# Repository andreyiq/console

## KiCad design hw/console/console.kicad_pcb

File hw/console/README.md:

# hw/console — схема платы v2 в KiCad 9

Открывать: `kicad hw/console/console.kicad_pro`.

## Статус: разработка, не финал

**Ничего из решённого не является окончательным.** Плата не изготовлена, срок
не горит, тираж не заказан — значит любую деталь, номинал, габарит, топологию
и сам выбор технологии можно и **нужно** пересматривать, если появился повод.

Отсюда рабочее правило: **когда во что-то упираемся — двигаем то, во что
упёрлись, а не проламываемся.** Не влезает деталь — меняем деталь. Не
складывается разводка — меняем размещение или габарит платы. Мешает принятое
раньше решение — обсуждаем его заново, а не обходим.

Записанное в этих документах — это состояние обсуждения на сегодня вместе с
обоснованием, а не приговор. Обоснование как раз затем и пишется: чтобы через
месяц было видно, на чём решение держится, и можно было честно проверить, не
рассыпалось ли оно. Уже так и вышло: планка «`ISAT` ≥ 2 А, `DCR` < 50 мΩ» была
записана как требование, а оказалась перестраховкой — живая плата Xassette
работает на 176 мΩ (02-power.md §5). Решение переписано.

Ссылки на источники (даташит, MangoPi, Xassette) при этом остаются жёсткими:
меняться может **наше** решение, но не факт, на который оно опирается.

## Источники истины

Ровно три, больше ничего:

| | |
|---|---|
| **Даташит** | `docs/mangopi/f133_datasheet_v1.2.pdf` и `docs/chips/<партномер>_<LCSC>.pdf` |
| **MangoPi** | `docs/mangopi/mq_sch_v1.6.pdf` — серийная плата на том же F133-A |
| **Xassette** | `../ref/Xassette-Asterisk/` — вторая живая плата на F133, и единственная опора, где есть **сама плата**, а не только схема: `hw/XassetteAsterisk.kicad_pcb` отвечает на вопросы про стек, термопад и переходные |

Всё остальное — не источник. В частности [`../BOARD-draft.md`](../BOARD-draft.md)
**недостоверен**: он писался по ходу дела, мешает проверенные числа с
рассуждениями, и в нём уже находилось прямое противоречие самому себе.
Ссылаться на него нельзя, он оставлен как список тем для перепроверки.
[`../TZ.md`](../TZ.md) отвечает только на вопрос «что должно быть на плате»,
[`../CHIPS.md`](../CHIPS.md) — «какие микросхемы», ни один из них не источник
электрических решений.

**Правило: ни одного номинала и ни одной цепи без ссылки на источник.** Если
факта нет ни в даташите, ни на двух платах — это не факт, а допущение, и оно
помечается как допущение вместе с тем, чем рискуем.

## Порядок работы — по блокам

Блок = микросхема (или группа) из [`../CHIPS.md`](../CHIPS.md). На каждый блок
заводится документ в [`blocks/`](blocks/) с жёсткой структурой:

1. **Микросхемы** — какие пункты CHIPS.md закрывает блок
2. **Из даташита** — выдержки с номером таблицы или параграфа
3. **MangoPi** — что реально сделано, с номером страницы и позициями
4. **Xassette** — то же, с refdes из нетлиста
5. **Расхождения** — где референсы спорят друг с другом или с даташитом
6. **Что рисуем** — решение, каждая строка со ссылкой на пункты выше
7. **Допущения и открытые вопросы** — всё, что не подтверждено источником

Итерация: собрать документ блока → обсудить открытые вопросы → дополнить
[`../CHIPS.md`](../CHIPS.md) закупкой → нарисовать блок → показать глазами →
ERC и netlist → следующий блок.

| Блок | Микросхемы (CHIPS.md) | Документ | Статус |
|---|---|---|---|
| 1 Кнопки | — | [01-buttons.md](blocks/01-buttons.md) | **нарисовано**, 10 деталей |
| 2 Питание | §2 `SY8089AAAC`×3, §3 `TP4056`, §7 движок, §8 банка, §10 power path | [02-power.md](blocks/02-power.md) | **нарисовано**, 48 деталей |
| 3 USB и FEL | §9 `USBLC6-2SC6` | [03-usb.md](blocks/03-usb.md) | **нарисовано**, 5 деталей |
| 4 Хранение | §6 `W25Q32` | [04-storage.md](blocks/04-storage.md) | **нарисовано**, 16 деталей |
| 5 Звук | §5 `PAM8301` | [05-audio.md](blocks/05-audio.md) | **нарисовано**, 11 деталей |
| 6 Дисплей | §4 подсветка | [06-display.md](blocks/06-display.md) | **нарисовано**, 13 деталей |
| 7 Такт и сброс | — | [07-clock-reset.md](blocks/07-clock-reset.md) | **нарисовано**, 10 деталей |
| 8 Развязка и КТ | §1 `F133-A` | [08-decoupling.md](blocks/08-decoupling.md) | **нарисовано**, 33 детали |
| 9 UART, JTAG, светодиод | — | [09-debug.md](blocks/09-debug.md) | **нарисовано**, 8 деталей |
| 10 Механика и плата | — | [10-mech.md](blocks/10-mech.md) | контур, механика посажена, разводки нет |

## Как устроен лист

**Один лист A2**, `console.kicad_sch`. F133 целиком в середине, обвязка вокруг
него девятью блоками в пунктирных рамках. Раскладка скопирована со стр. 3 схемы
MangoPi (`docs/mangopi/mq_sch_v1.6.pdf`) — это плата на том же чипе, и она
устроена так же.

Правило раскладки: **блок стоит с той стороны корпуса, откуда выходят его
выводы.** Символ повторяет корпус, поэтому сторона известна заранее:

| Выводы | Сторона | Блок |
|---|---|---|
| 1..6, 118..128 `PG` | лево-верх и верх-лево | 1 Кнопки |
| 7..13 `PF`, 14..19 `PC` | лево | 4 Хранение |
| 20..30 PLL/DCXO/RTC/LDO | лево-низ | 7 Такт и сброс |
| 31..45 `PE` | лево-низ и низ-лево | 9 UART, JTAG, светодиоды |
| 46..51 SYS/DRAM | низ-центр | 8 Развязка и контрольные точки |
| 52..76 `PD` | низ-право и право-низ | 6 Дисплей |
| 87..100 аудио | право-верх | 5 Звук |
| 101..117 ADC/USB/CORE | верх | 2 Питание, 3 USB и FEL |

Раскладка задаёт только геометрию. Что внутри блока — в его документе
в [`blocks/`](blocks/).

## Как соединяется

Проводов между блоками нет — всё на **глобальных метках**, как у MangoPi. Для
128-выводного чипа это единственный читаемый вариант: цепь называется один раз
у вывода F133 и один раз у потребителя, а не тянется через весь лист.
Локальные провода — только внутри блока (делитель, RC, развязка).

## Библиотеки

Обе локальные, лежат в `lib/`, подключены через `${KIPRJMOD}` — проект
открывается на любой машине без установки библиотек.

| | |
|---|---|
| `lib/console.kicad_sym` | символ F133-A. Генерируется, руками не править |
| `lib/parts.kicad_sym` | то, чего нет в штатных библиотеках: `SY8089AAAC` (по даташиту) и рельсы `VSYS`, `+0V9`. Пишется руками |
| `lib/console.pretty` | футпринты платы. `eLQFP-128 ... EPAD_5.72mm` взят из `../lib/allwinner_SiPs_kicad_lib` и обновлён до формата KiCad 9 |

### Символ F133-A

Собирается скриптом из распиновки даташита:

```
python3 hw/console/tools/gen_f133_sym.py
```

Скрипт правит **две** копии символа: `lib/console.kicad_sym` и вшитую в
`console.kicad_sch` секцию `lib_symbols` — KiCad библиотеку при открытии не
перечитывает, и правка распиновки, не доехавшая до листа, разъезжается молча.

129 выводов (128 + `EPAD`), один юнит, корпус 119 × 114 мм. Выводы разложены
**в порядке нумерации eLQFP128** — 1..32 слева сверху вниз, 33..64 снизу слева
направо, 65..96 справа снизу вверх, 97..128 сверху справа налево. Проверено по
футпринту: лапка 33 в левом нижнем углу, 97 в правом верхнем. То есть символ
читается как сам корпус, и при разводке сразу видно, с какой стороны выходит
цепь. Функциональные зоны нарисованы поверх — короткой линией от края и
подписью.

Исходник распиновки — `F133_Datasheet_V1.2.pdf`, таблица 4-2. Библиотека
Xassette (`../ref/Xassette-Asterisk/hw/lib/F133.lib`) использовалась для
сверки, в ней нашлись три расхождения с даташитом, здесь они исправлены:

| Вывод | У Xassette | В даташите |
|---|---|---|
| 47 | `DZQ` | `NC` — но обе платы ставят туда 240 Ω, поэтому тип `passive` и резистор мы тоже ставим (08-decoupling.md §5) |
| 51 | `VDD-SYS0` (дубль) | `VDD-SYS1` |
| 25 | `XX32KIN` | `X32KIN` |

Плюс к этому в символе:

- **выводы 107–111 помечены `no_connect`** — CVBS IN есть только у F133-B.
  У даташита на это отдельная таблица различий версий, Table 7-1 на стр. 74:
  «107 | NC | VCC-TVIN». Обе референсные платы вывод 107 подключают, потому
  что рисовались и под F133-B; разбор — 08-decoupling.md §2.4;
- **`EPAD` = `GND`** — отдельных выводов земли у корпуса нет, вся цифровая
  земля идёт через термопад. Значит термопад обязан быть пришит переходными
  к нижнему слою, это не только теплоотвод;
- **вывод 27 `RESET`** — тип `I, OD`, домен **`VCC-RTC` = 1.8 В**, не 3.3.
  Подтяжка и кнопка сброса должны сидеть на `+1V8`.

## Каркас листа

```
python3 hw/console/tools/scaffold.py
```

Одноразовый скрипт: создаёт лист, рамки блоков, таблицы библиотек и ставит
F133. Уже существующие файлы **не трогает** — схему, которую правили руками,
он не затрёт. UUID детерминированные, поэтому на чистой папке результат
повторяется побайтово.

`console.kicad_pro` скриптом не создаётся — он взят от платы v1 и почищен.

Две грабли, на которые скрипты уже наступили и больше не наступают:

- **координаты символа обязаны быть кратны 1.27 мм.** Середина A2 — это 297.0,
  что не кратно, и все 129 выводов уезжают с сетки (`endpoint_off_grid`).
  Берём 297.18 = 117 × 2.54.
- **`(justify center)` в свойстве символа парсер библиотеки не принимает** —
  библиотека молча перестаёт грузиться целиком. По центру и так по умолчанию,
  просто не указывать.

## Сверка с референсом Xassette

`kicad-cli` схему Xassette не открывает — это legacy-формат KiCad 5. Поэтому
свой разбор:

```
python3 hw/console/tools/xassette_net.py U1 U3 U4 U5   # цепь на каждом выводе
python3 hw/console/tools/xassette_net.py --net +1V8 +3V3   # состав цепи
```

Цепи собираются union-find'ом по концам проводов, junction'ам, меткам и
power-символам.

## Сверка со схемой MangoPi

Она есть только в PDF, но PDF векторный, поэтому её тоже читаем как схему, а
не как картинку:

```
python3 hw/console/tools/mangopi_net.py --page 3 --trace 520 710   # цепь в точке
python3 hw/console/tools/mangopi_net.py --page 3 --at 520 710      # что рядом
python3 hw/console/tools/mangopi_net.py --page 3 --label VCC-DRAM  # цепь по имени
```

`pdftocairo -svg` отдаёт точные концы каждого отрезка; провода там зелёные,
точки соединения — залитые кружки того же цвета. Отрезки объединяются в цепь
по совпадению концов, а касание конца к середине другого отрезка считается
соединением **только** при наличии точки. Имена цепей и номера выводов берутся
из `pdftotext -bbox` и привязываются к проводу по координатам.

Так надо потому, что чтение кропов глазами дважды подряд дало неверный ответ:
резистор `R40 680K` был принят за делитель соседнего преобразователя (номинал
совпадает), а кнопка сброса `S2` не найдена, потому что искалась не на той
странице. Кроп через `pdftoppm` остаётся, но уже как иллюстрация к тому, что
посчитал нетлистер.

Что уже вытащено этими двумя способами — в документах блоков, [`blocks/`](blocks/).

## Плата

```
python3 hw/console/tools/pcb01_outline.py    # контур, крепёж, разметка
# в KiCad: Update PCB from Schematic (F8)    — CLI для этого нет
python3 hw/console/tools/pcb01_outline.py    # F8 сносит крепёж `H*`, вернуть
python3 hw/console/tools/pcb00_sync.py       # корпуса под то, что в схеме
python3 hw/console/tools/pcb02_place.py      # посадка механики, с блокировкой
python3 hw/console/tools/pcb03_blocks.py     # черновая раскладка блоков
python3 hw/console/tools/pcb04_fine.py      # точная посадка, где место задано
python3 hw/console/tools/pcb05_text.py      # ссылки на Fab, шелкографии нет
python3 hw/console/tools/pcb_run.py         # разводка целиком и сводка
```

Последний шаг — весь круг разводки одной командой: веер из-под F133, свой
волновой трассировщик, добор поверх готового, заливки, сшивка и добивка земли,
и в конце сводка с DRC. Добор идёт дольше всего остального вместе, поэтому в
обычной итерации `--no-more` (210 секунд против получаса). Подробно и с
замерами — [10-mech.md §8.3](blocks/10-mech.md).

Все шесть шагов размещения идемпотентны и не трогают чужого: `pcb01` заново кладёт только
свою графику и крепёж, `pcb02` и `pcb04` блокируют то, что посадили, `pcb03`
двигает исключительно незаблокированное. Значит ручную правку размещения они
не затрут.

Правила процесса, координаты и открытые вопросы — [10-mech.md](blocks/10-mech.md).
Собственные правила DRC (одно: площадкам `U1` между собой разрешено 0.15 мм,
потому что таков сам `eLQFP-128`) — в `console.kicad_dru`.

Проверка платы:

```
python3 hw/console/tools/audit_pcb.py
```

Семнадцать проверок того, чего нет в DRC: зона банки, развязка у своих выводов,
минимальное сверло, что под панелью на лице только разъём шлейфа, раскладка
баков по даташиту, состав платы против схемы цепь за цепью. DRC она вызывает
сама и печатает сводкой. Каждая проверка показывает, сколько объектов
посмотрела, — иначе не отличить «чисто» от «сломано».

## Проверка

```
python3 hw/console/tools/audit.py
```

Шестнадцать проверок, каждая печатает, сколько объектов посмотрела. Половину
из них ERC не делает вовсе: Т-образное соединение без точки, метка не на
проводе, наложенные провода, деталь без поля `Источник`, корпус без площадки
под вывод символа, похожие имена цепей. Сейчас все шестнадцать дают ноль.

Отдельно то же самое руками:

```
kicad-cli sch erc           -o /tmp/erc.rpt      hw/console/console.kicad_sch
kicad-cli sch export netlist -o /tmp/console.net  hw/console/console.kicad_sch
kicad-cli sch export pdf     -o /tmp/console.pdf  hw/console/console.kicad_sch
```

**Нарисованы все девять блоков: ERC даёт 0 нарушений.** Число падало по мере
работы: 160 до блока 8, 104 до блока 3, 62 до блока 1, 46 до блока 5, 23 до
блока 9. Ноль означает ровно одно — у каждого из 128 выводов F133 есть либо
цепь, либо крестик «не подключать», и ни одна цепь не осталась висеть в
воздухе. Это не означает, что схема верна: ERC не знает ни номиналов, ни того,
что делает софт.

**Netlist смотреть обязательно, картинки мало.** Провод, нарисованный
правильно, может оказаться разорванным: KiCad считает соединением только конец
провода или точку с junction, поэтому провод обязан быть разрезан там, где к
нему что-то подключается. На печати такая ошибка неотличима от исправной
схемы — в блоке 2 так молча распалась обратная связь канала 0.9 В.

## Как рисуются блоки

Весь чертёж воспроизводится из скриптов:

```
for b in 01_buttons 02_power 03_usb 04_storage 05_audio \
         06_display 07_clock_reset 08_decoupling 09_debug; do
    python3 hw/console/tools/block$b.py
done
```

Прогон в этом порядке даёт **побайтово тот же файл**, что лежит в репозитории:
проверено. Порядок важен только для побайтовости — содержимое от него не
зависит, каждый блок трогает лишь свою рамку и свои зоны у выводов F133.

Каждый блок рисует свой скрипт `tools/blockNN_*.py`, общая машинерия — в
`tools/kicadsch.py`. Модуль печатает те же s-выражения, что писались бы руками;
библиотек KiCad в нём нет. Он же считает координаты выводов при повороте
символа — попасть в вывод надо точно, а руками это и есть главный источник
молчаливых обрывов. Скрипт блока идемпотентный:
перед вставкой выкидывает из схемы всё, что лежит внутри рамки своего блока, и
кладёт заново, — соседние блоки при этом не страдают, а UUID детерминированные,
поэтому повторный запуск не даёт diff'а на пустом месте.

У каждой детали заполнено поле `Источник` — раздел документа блока, откуда взят
номинал. Правило «ни одного номинала без ссылки на источник» проверяется прямо
по схеме, а не на доверии.

Грабли, на которые скрипты уже наступили и больше не наступают:

- `(hide yes)` внутри `(effects)` **не срабатывает, если рядом нет
  `(justify)`** — служебные ссылки `#PWR`/`#FLG` из-за этого печатались в PDF;
- **номер блока обязан входить в ссылку** служебного символа (`#PWR700`, а не
  `#PWR000`): иначе каждый блок начинает нумерацию с нуля и выдаёт ссылки,
  уже занятые соседом;
- `✓` и подобные знаки штриховой шрифт KiCad не рисует — в PDF выходит пустой
  квадрат. В подписях только то, что есть в шрифте.

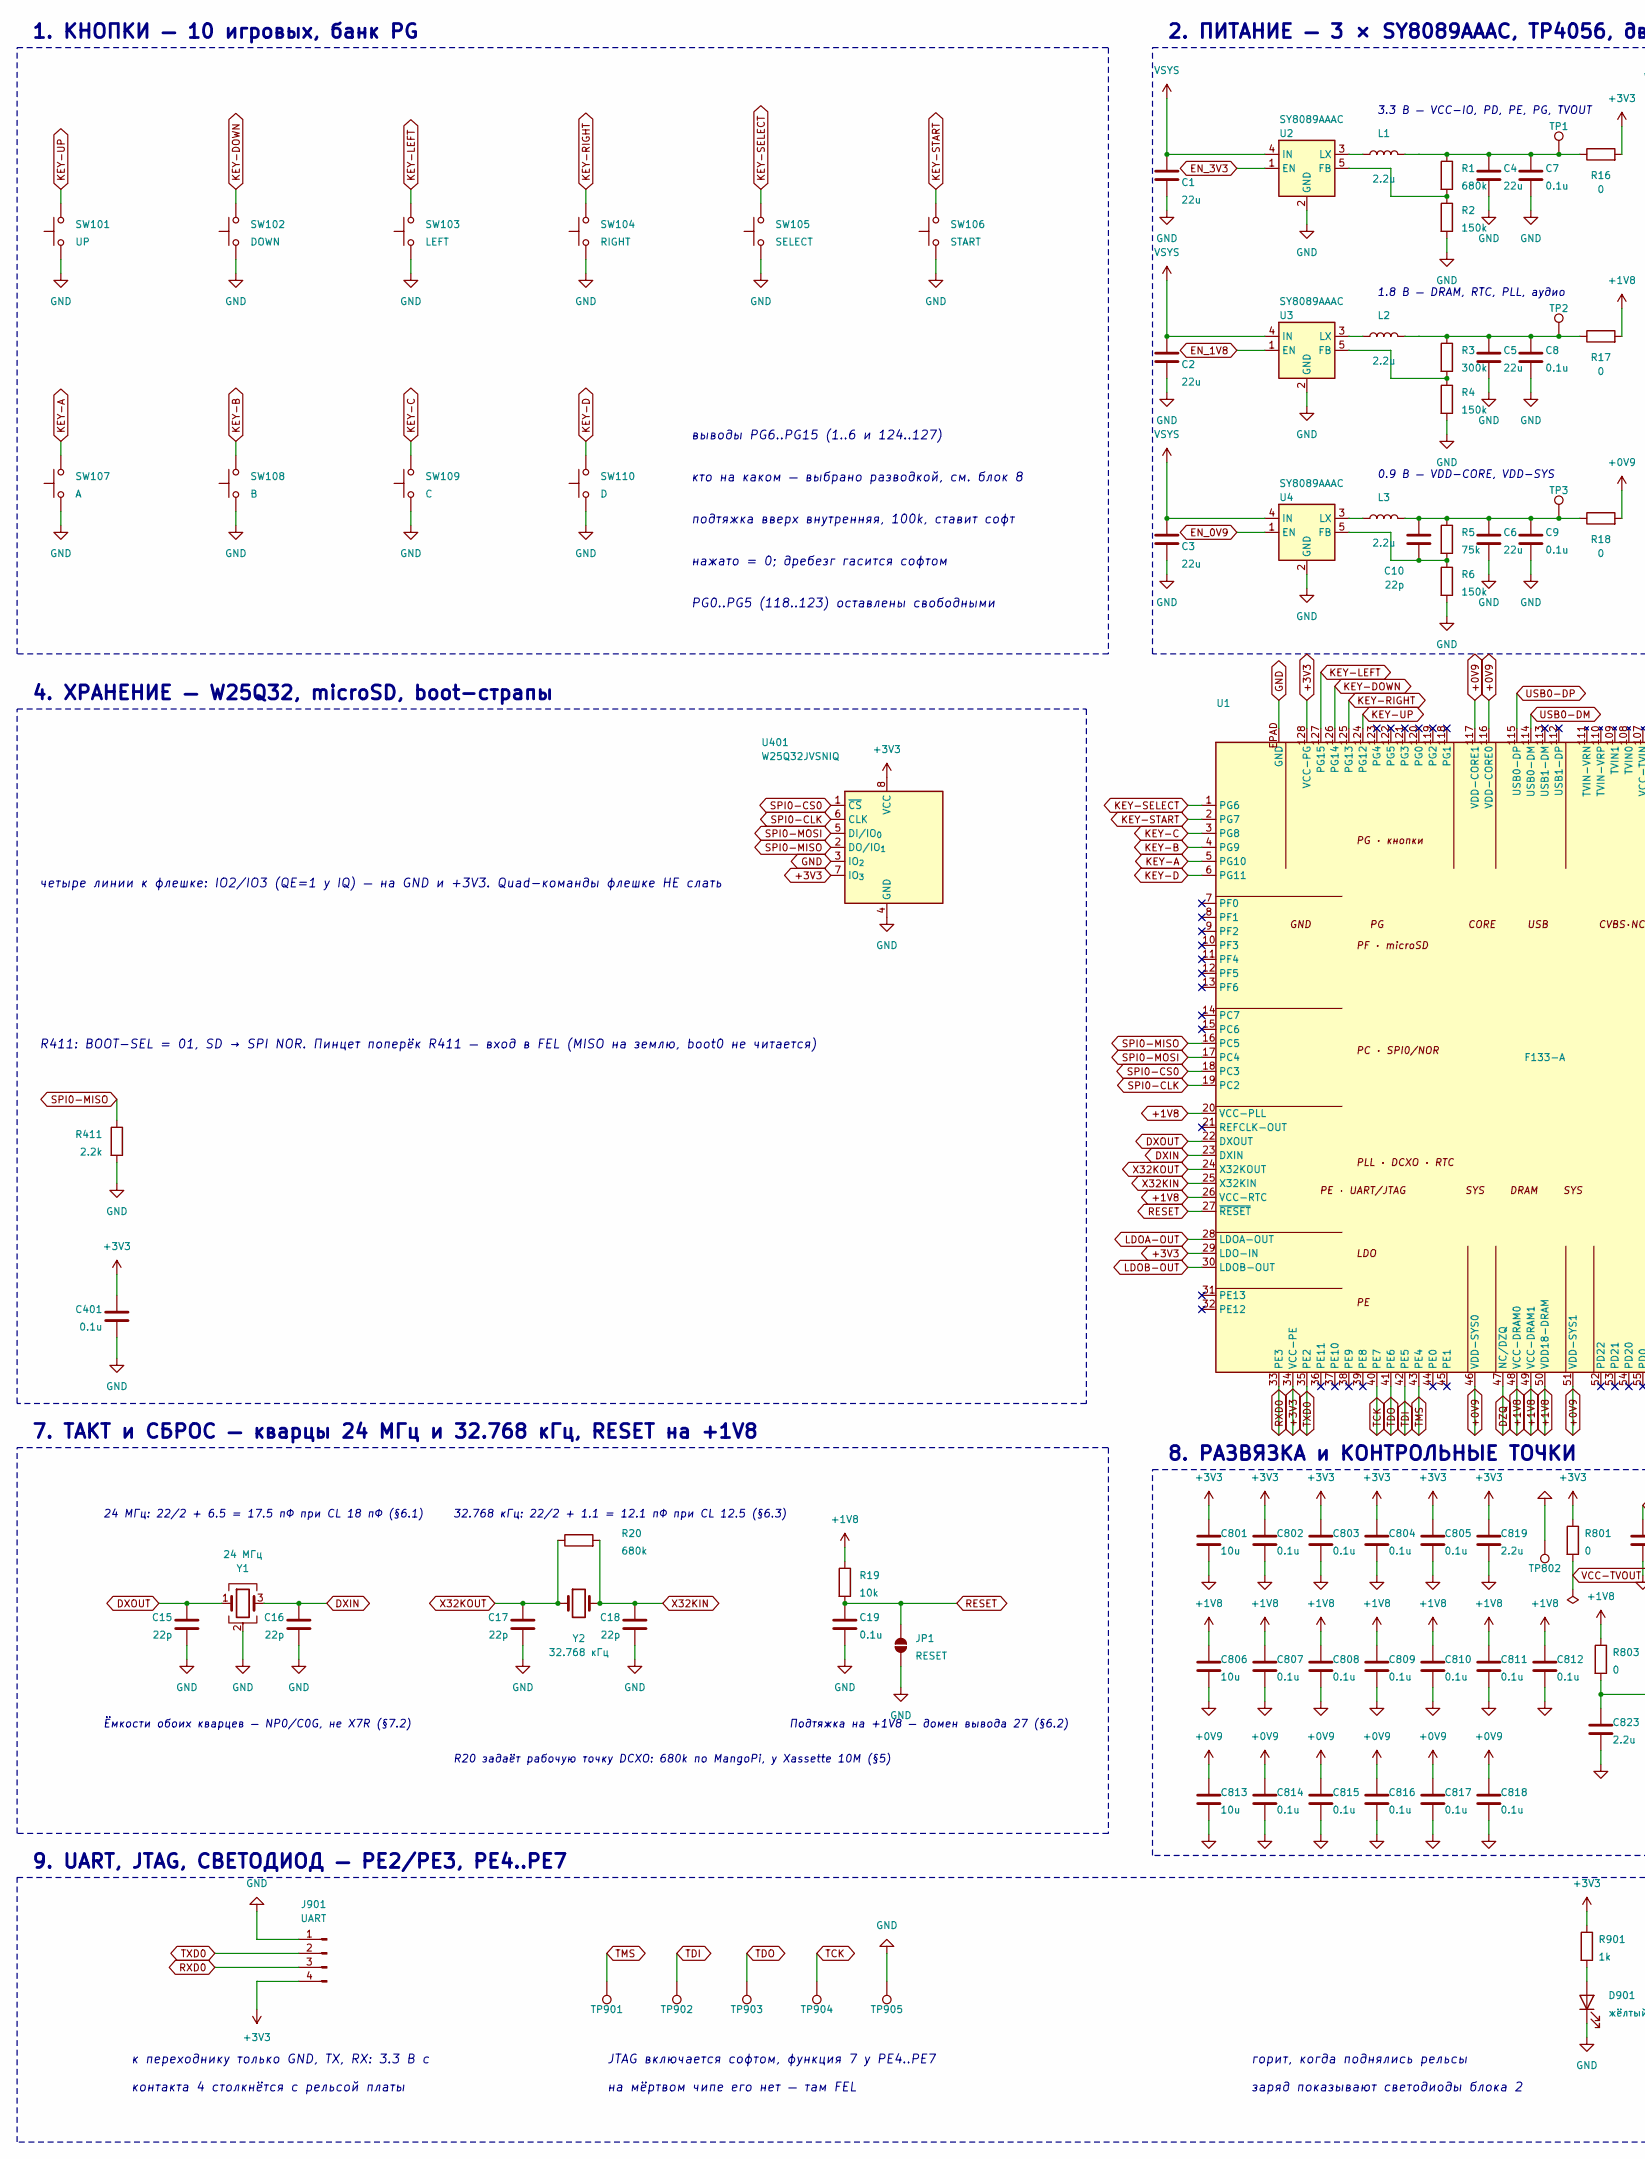
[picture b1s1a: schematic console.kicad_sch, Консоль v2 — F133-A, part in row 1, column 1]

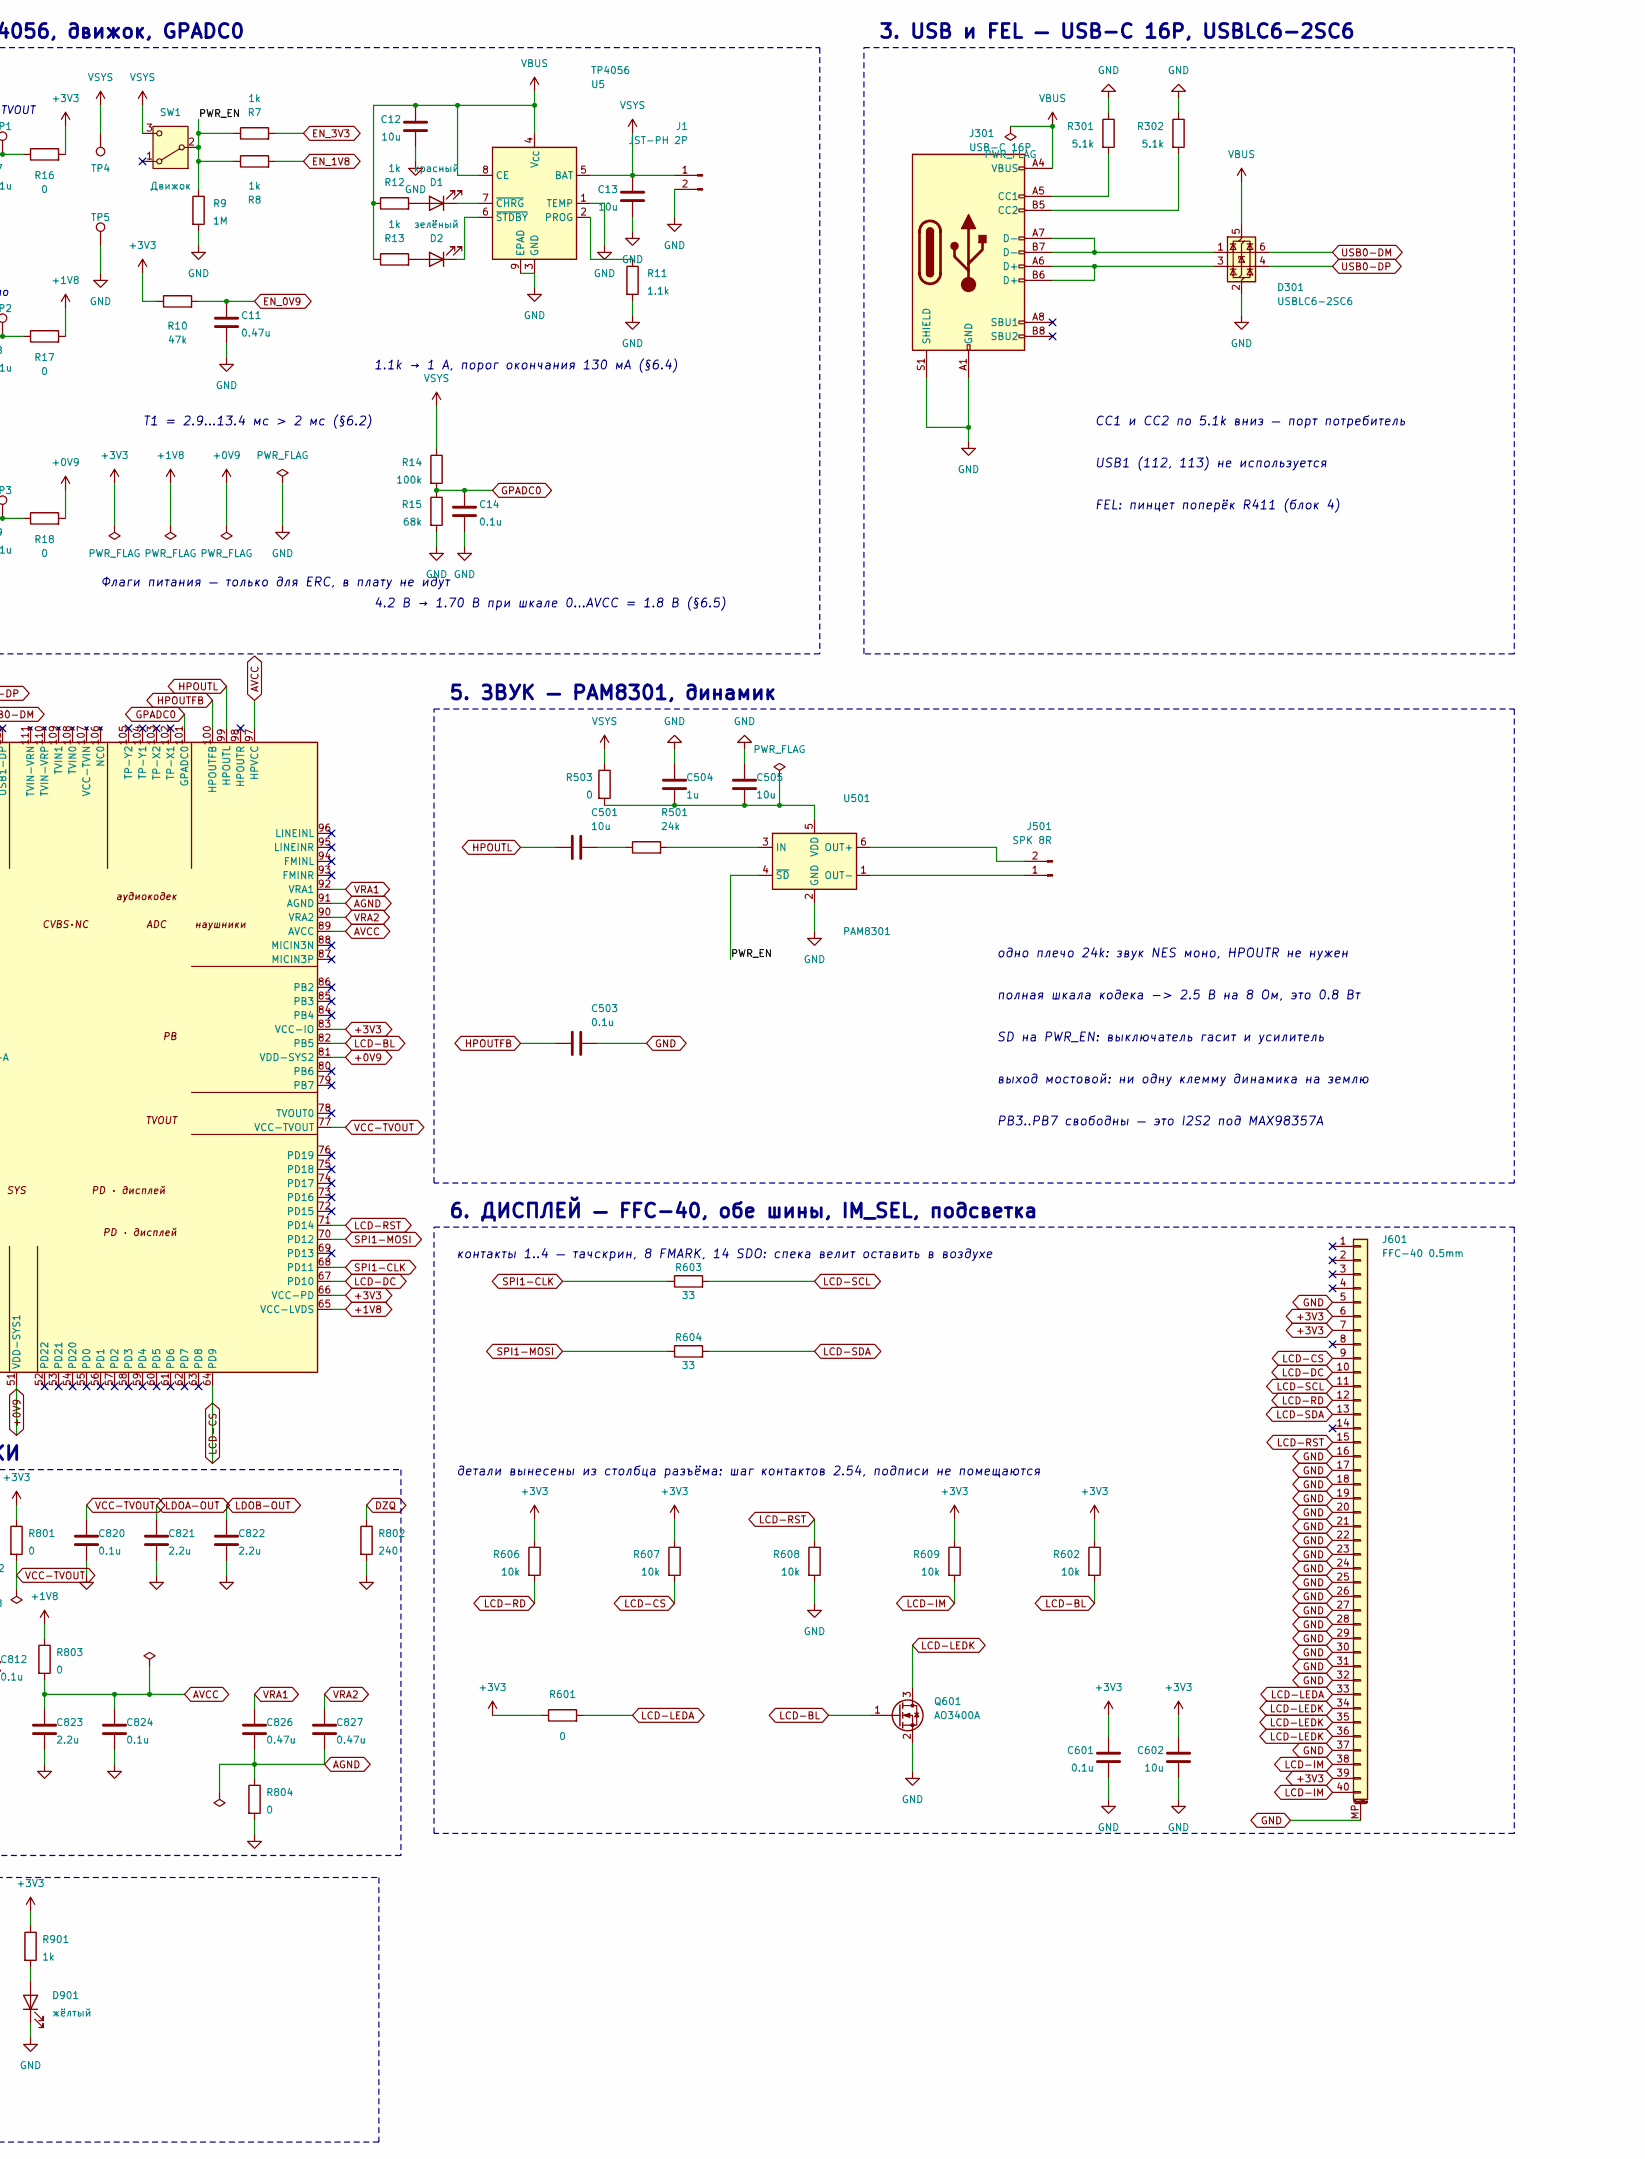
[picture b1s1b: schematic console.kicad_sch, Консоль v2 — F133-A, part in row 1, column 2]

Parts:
C1, C2, C3, C4, C5, C6: 22u; C_0805_2012Metric_Pad1.18x1.45mm_HandSolder
C7, C8, C9, C14, C19, C401, C503, C601: 0.1u; C_0805_2012Metric_Pad1.18x1.45mm_HandSolder
C10, C15, C16, C17, C18: 22p; C_0805_2012Metric_Pad1.18x1.45mm_HandSolder
C11: 0.47u; C_0805_2012Metric_Pad1.18x1.45mm_HandSolder
C12, C13, C501, C505, C602: 10u; C_0805_2012Metric_Pad1.18x1.45mm_HandSolder
C504: 1u; C_0805_2012Metric_Pad1.18x1.45mm_HandSolder
C801, C806, C813: 10u; C_0805_2012Metric
C802, C803, C804, C805, C807, C808, C809, C810, C811, C812, C814, C815, C816, C817, C818, C820, C824: 0.1u; C_0805_2012Metric
C819, C821, C822, C823: 2.2u; C_0805_2012Metric
C826, C827: 0.47u; C_0805_2012Metric
D1: красный; LED_0805_2012Metric_Pad1.15x1.40mm_HandSolder
D2: зелёный; LED_0805_2012Metric_Pad1.15x1.40mm_HandSolder
D301: USBLC6-2SC6; SOT-23-6; LCSC C2687116
D901: жёлтый; LED_0805_2012Metric_Pad1.15x1.40mm_HandSolder
J1: JST-PH 2P; JST_PH_B2B-PH-SM4-TB_1x02-1MP_P2.00mm_Vertical
J301: USB-C 16P; USB_C_Receptacle_HRO_TYPE-C-31-M-12; LCSC C165948
J501: SPK 8R; PinHeader_1x02_P2.54mm_Vertical
J601: FFC-40 0.5mm; Hirose_FH12-40S-0.5SH_1x40-1MP_P0.50mm_Horizontal; LCSC C202114
J901: UART; PinHeader_1x04_P2.54mm_Vertical
JP1: RESET; SolderJumper-2_P1.3mm_Open_Pad1.0x1.5mm
L1, L2, L3: 2.2u; L_Sunlord_SWPA3015S
Q601: AO3400A; SOT-23
R1, R20: 680k; R_0805_2012Metric_Pad1.20x1.40mm_HandSolder
R2, R4, R6: 150k; R_0805_2012Metric_Pad1.20x1.40mm_HandSolder
R3: 300k; R_0805_2012Metric_Pad1.20x1.40mm_HandSolder
R5: 75k; R_0805_2012Metric_Pad1.20x1.40mm_HandSolder
R7, R8, R12, R13, R901: 1k; R_0805_2012Metric_Pad1.20x1.40mm_HandSolder
R9: 1M; R_0805_2012Metric_Pad1.20x1.40mm_HandSolder
R10: 47k; R_0805_2012Metric_Pad1.20x1.40mm_HandSolder
R11: 1.1k; R_0805_2012Metric_Pad1.20x1.40mm_HandSolder
R14: 100k; R_0805_2012Metric_Pad1.20x1.40mm_HandSolder
R15: 68k; R_0805_2012Metric_Pad1.20x1.40mm_HandSolder
R16, R17, R18, R503, R601, R801, R803, R804: 0; R_0805_2012Metric_Pad1.20x1.40mm_HandSolder
R19, R602, R606, R607, R608, R609: 10k; R_0805_2012Metric_Pad1.20x1.40mm_HandSolder
R301, R302: 5.1k; R_0805_2012Metric_Pad1.20x1.40mm_HandSolder
R411: 2.2k; R_0805_2012Metric_Pad1.20x1.40mm_HandSolder
R501: 24k; R_0805_2012Metric_Pad1.20x1.40mm_HandSolder
R603, R604: 33; R_0805_2012Metric_Pad1.20x1.40mm_HandSolder
R802: 240; R_0805_2012Metric_Pad1.20x1.40mm_HandSolder
SW1: Движок; SW_SPDT_Shouhan_MSK12C02
SW101: UP; SW_SPST_PTS645Sx43SMTR92
SW102: DOWN; SW_SPST_PTS645Sx43SMTR92
SW103: LEFT; SW_SPST_PTS645Sx43SMTR92
SW104: RIGHT; SW_SPST_PTS645Sx43SMTR92
SW105: SELECT; SW_SPST_PTS645Sx43SMTR92
SW106: START; SW_SPST_PTS645Sx43SMTR92
SW107: A; SW_SPST_PTS645Sx43SMTR92
SW108: B; SW_SPST_PTS645Sx43SMTR92
SW109: C; SW_SPST_PTS645Sx43SMTR92
SW110: D; SW_SPST_PTS645Sx43SMTR92
TP1: +3V3; TestPoint_Pad_D1.5mm
TP2: +1V8; TestPoint_Pad_D1.5mm
TP3: +0V9; TestPoint_Pad_D1.5mm
TP4: VSYS; TestPoint_Pad_D1.5mm
TP5, TP802, TP905: GND; TestPoint_Pad_D1.5mm
TP901: TMS; TestPoint_Pad_D1.5mm
TP902: TDI; TestPoint_Pad_D1.5mm
TP903: TDO; TestPoint_Pad_D1.5mm
TP904: TCK; TestPoint_Pad_D1.5mm
U1: F133-A; eLQFP-128_14x14_Pitch0.4mm_EPAD_5.72mm
U2, U3, U4: SY8089AAAC; SOT-23-5_HandSoldering; LCSC C78988
U5: TP4056; SOIC-8-1EP_3.9x4.9mm_P1.27mm_EP2.41x3.3mm; LCSC C16581
U401: W25Q32JVSNIQ; SOIC-8_3.9x4.9mm_P1.27mm
U501: PAM8301; SOT-23-6; LCSC C3001605
Y1: 24 МГц; Crystal_SMD_3225-4Pin_3.2x2.5mm
Y2: 32.768 кГц; Crystal_SMD_3215-2Pin_3.2x1.5mm

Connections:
+0V9: C813.1, C814.1, C815.1, C816.1, C817.1, C818.1, R18.2, U1.46 (VDD-SYS0), U1.51 (VDD-SYS1), U1.81 (VDD-SYS2), U1.116 (VDD-CORE0), U1.117 (VDD-CORE1)
+1V8: C806.1, C807.1, C808.1, C809.1, C810.1, C811.1, C812.1, R17.2, R19.1, R803.1, U1.20 (VCC-PLL), U1.26 (VCC-RTC), U1.48 (VCC-DRAM0), U1.49 (VCC-DRAM1), U1.50 (VDD18-DRAM), U1.65 (VCC-LVDS)
+3V3: C401.1, C601.1, C602.1, C801.1, C802.1, C803.1, C804.1, C805.1, C819.1, J601.6, J601.7, J601.39, J901.4, R10.1, R16.2, R601.1, R602.1, R606.1, R607.1, R609.1, R801.1, R901.1, U1.29 (LDO-IN), U1.34 (VCC-PE), U1.66 (VCC-PD), U1.83 (VCC-IO), U1.128 (VCC-PG), U401.7 (IO_{3}), U401.8 (VCC)
/PWR_EN: R7.1, R8.1, R9.1, SW1.2 (B), U501.4 (~SD)
DXIN: C16.1, U1.23 (DXIN), Y1.3
DXOUT: C15.1, U1.22 (DXOUT), Y1.1
DZQ: R802.1, U1.47 (NC/DZQ)
EN_0V9: C11.1, R10.2, U4.1 (EN)
EN_1V8: R8.2, U3.1 (EN)
EN_3V3: R7.2, U2.1 (EN)
GND: C1.2, C2.2, C3.2, C4.2, C5.2, C6.2, C7.2, C8.2, C9.2, C11.2, C12.2, C13.2, C14.2, C15.2, C16.2, C17.2, C18.2, C19.2, C401.2, C503.2, C504.1, C505.1, C601.2, C602.2, C801.2, C802.2, C803.2, C804.2, C805.2, C806.2, C807.2, C808.2, C809.2, C810.2, C811.2, C812.2, C813.2, C814.2, C815.2, C816.2, C817.2, C818.2, C819.2, C820.2, C821.2, C822.2, C823.2, C824.2, D301.2 (GND), D901.1 (K), J1.2, J301.A1 (GND), J301.A12 (GND), J301.B1 (GND), J301.B12 (GND), J301.S1 (SHIELD), J601.5, J601.16, J601.17, J601.18, J601.19, J601.20, J601.21, J601.22, J601.23, J601.24, J601.25, J601.26, J601.27, J601.28, J601.29, J601.30, J601.31, J601.32, J601.37, J601.MP (MountPin), J901.1, JP1.1 (A), Q601.2 (S), R2.2, R4.2, R6.2, R9.2, R11.2, R15.2, R301.1, R302.1, R411.2, R608.2, R802.2, R804.2, SW101.1, SW102.1, SW103.1, SW104.1, SW105.1, SW106.1, SW107.1, SW108.1, SW109.1, SW110.1, TP5.1, TP802.1, TP905.1, U1.EPAD (GND), U2.2 (GND), U3.2 (GND), U4.2 (GND), U5.1 (TEMP), U5.3 (GND), U5.9 (EPAD), U401.3 (IO_{2}), U401.4 (GND), U501.2 (GND), Y1.2 (G), Y1.4 (G)
GPADC0: C14.1, R14.2, R15.1, U1.101 (GPADC0)
HPOUTFB: C503.1, U1.100 (HPOUTFB)
HPOUTL: C501.1, U1.99 (HPOUTL)
KEY-A: SW107.2, U1.5 (PG10)
KEY-B: SW108.2, U1.4 (PG9)
KEY-C: SW109.2, U1.3 (PG8)
KEY-D: SW110.2, U1.6 (PG11)
KEY-DOWN: SW102.2, U1.126 (PG14)
KEY-LEFT: SW103.2, U1.127 (PG15)
KEY-RIGHT: SW104.2, U1.125 (PG13)
KEY-SELECT: SW105.2, U1.1 (PG6)
KEY-START: SW106.2, U1.2 (PG7)
KEY-UP: SW101.2, U1.124 (PG12)
LCD-BL: Q601.1 (G), R602.2, U1.82 (PB5)
LCD-CS: J601.9, R607.2, U1.64 (PD9)
LCD-DC: J601.10, U1.67 (PD10)
LCD-IM: J601.38, J601.40, R609.2
LCD-LEDA: J601.33, R601.2
LCD-LEDK: J601.34, J601.35, J601.36, Q601.3 (D)
LCD-RD: J601.12, R606.2
LCD-RST: J601.15, R608.1, U1.71 (PD14)
LCD-SCL: J601.11, R603.2
LCD-SDA: J601.13, R604.2
LDOA-OUT: C821.1, U1.28 (LDOA-OUT)
LDOB-OUT: C822.1, U1.30 (LDOB-OUT)
unnamed: C4.1, C7.1, L1.2, R1.1, R16.1, TP1.1
unnamed: C5.1, C8.1, L2.2, R3.1, R17.1, TP2.1
unnamed: C6.1, C9.1, C10.1, L3.2, R5.1, R18.1, TP3.1
unnamed: C501.2, R501.1
unnamed: D1.2 (A), R12.2
unnamed: D1.1 (K), U5.7 (~CHRG)
unnamed: D2.2 (A), R13.2
unnamed: D2.1 (K), U5.6 (~STDBY)
unnamed: D301.1 (I/O1), J301.A7 (D-), J301.B7 (D-)
unnamed: D301.3 (I/O2), J301.A6 (D+), J301.B6 (D+)
unnamed: D901.2 (A), R901.2
unnamed: J301.A5 (CC1), R301.2
unnamed: J301.B5 (CC2), R302.2
unnamed: J501.1, U501.1 (OUT-)
unnamed: J501.2, U501.6 (OUT+)
unnamed: R1.2, R2.1, U2.5 (FB)
unnamed: L1.1, U2.3 (LX)
unnamed: R3.2, R4.1, U3.5 (FB)
unnamed: L2.1, U3.3 (LX)
unnamed: C10.2, R5.2, R6.1, U4.5 (FB)
unnamed: L3.1, U4.3 (LX)
unnamed: R11.1, U5.2 (PROG)
unnamed: R501.2, U501.3 (IN)
unnamed: C504.2, C505.2, R503.2, U501.5 (VDD)
RESET: C19.1, JP1.2 (B), R19.2, U1.27 (~RESET)
RXD0: J901.3, U1.33 (PE3)
SPI0-CLK: U1.19 (PC2), U401.6 (CLK)
SPI0-CS0: U1.18 (PC3), U401.1 (~CS)
SPI0-MISO: R411.1, U1.16 (PC5), U401.2 (DO/IO_{1})
SPI0-MOSI: U1.17 (PC4), U401.5 (DI/IO_{0})
SPI1-CLK: R603.1, U1.68 (PD11)
SPI1-MOSI: R604.1, U1.70 (PD12)
TCK: TP904.1, U1.40 (PE7)
TDI: TP902.1, U1.42 (PE5)
TDO: TP903.1, U1.41 (PE6)
TMS: TP901.1, U1.43 (PE4)
TXD0: J901.2, U1.35 (PE2)
USB0-DM: D301.6 (I/O1), U1.114 (USB0-DM)
USB0-DP: D301.4 (I/O2), U1.115 (USB0-DP)
VBUS: C12.1, D301.5 (VBUS), J301.A4 (VBUS), J301.A9 (VBUS), J301.B4 (VBUS), J301.B9 (VBUS), R12.1, R13.1, U5.4 (V_{CC}), U5.8 (CE)
VRA1: C826.1, U1.92 (VRA1)
VRA2: C827.1, U1.90 (VRA2)
VSYS: C1.1, C2.1, C3.1, C13.1, J1.1, R14.1, R503.1, SW1.3 (C), TP4.1, U2.4 (IN), U3.4 (IN), U4.4 (IN), U5.5 (BAT)
X32KIN: C18.1, R20.2, U1.25 (X32KIN), Y2.2
X32KOUT: C17.1, R20.1, U1.24 (X32KOUT), Y2.1

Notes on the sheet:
1. КНОПКИ — 10 игровых, банк PG
2. ПИТАНИЕ — 3 × SY8089AAAC, TP4056, движок, GPADC0
3. USB и FEL — USB-C 16P, USBLC6-2SC6
4. ХРАНЕНИЕ — W25Q32, microSD, boot-страпы
5. ЗВУК — PAM8301, динамик
6. ДИСПЛЕЙ — FFC-40, обе шины, IM_SEL, подсветка
7. ТАКТ и СБРОС — кварцы 24 МГц и 32.768 кГц, RESET на +1V8
8. РАЗВЯЗКА и КОНТРОЛЬНЫЕ ТОЧКИ
9. UART, JTAG, СВЕТОДИОД — PE2/PE3, PE4..PE7
выводы PG6..PG15 (1..6 и 124..127)
кто на каком — выбрано разводкой, см. блок 8
подтяжка вверх внутренняя, 100k, ставит софт
нажато = 0; дребезг гасится софтом
PG0..PG5 (118..123) оставлены свободными
одно плечо 24k: звук NES моно, HPOUTR не нужен
полная шкала кодека -> 2.5 В на 8 Ом, это 0.8 Вт
SD на PWR_EN: выключатель гасит и усилитель
выход мостовой: ни одну клемму динамика на землю
PB3..PB7 свободны — это I2S2 под MAX98357A
24 МГц: 22/2 + 6.5 = 17.5 пФ при CL 18 пФ (§6.1)
32.768 кГц: 22/2 + 1.1 = 12.1 пФ при CL 12.5 (§6.3)
Подтяжка на +1V8 — домен вывода 27 (§6.2)
Ёмкости обоих кварцев — NP0/C0G, не X7R (§7.2)
R20 задаёт рабочую точку DCXO: 680k по MangoPi, у Xassette 10M (§5)
к переходнику только GND, TX, RX: 3.3 В с
контакта 4 столкнётся с рельсой платы
JTAG включается софтом, функция 7 у PE4..PE7
на мёртвом чипе его нет — там FEL
горит, когда поднялись рельсы
заряд показывают светодиоды блока 2
CC1 и CC2 по 5.1k вниз — порт потребитель
USB1 (112, 113) не используется
FEL: пинцет поперёк R411 (блок 4)
четыре линии к флешке: IO2/IO3 (QE=1 у IQ) — на GND и +3V3. Quad-команды флешке НЕ слать
R411: BOOT-SEL = 01, SD → SPI NOR. Пинцет поперёк R411 — вход в FEL (MISO на землю, boot0 не читается)
контакты 1..4 — тачскрин, 8 FMARK, 14 SDO: спека велит оставить в воздухе
детали вынесены из столбца разъёма: шаг контактов 2.54, подписи не помещаются
3.3 В — VCC-IO, PD, PE, PG, TVOUT
1.8 В — DRAM, RTC, PLL, аудио
0.9 В — VDD-CORE, VDD-SYS

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
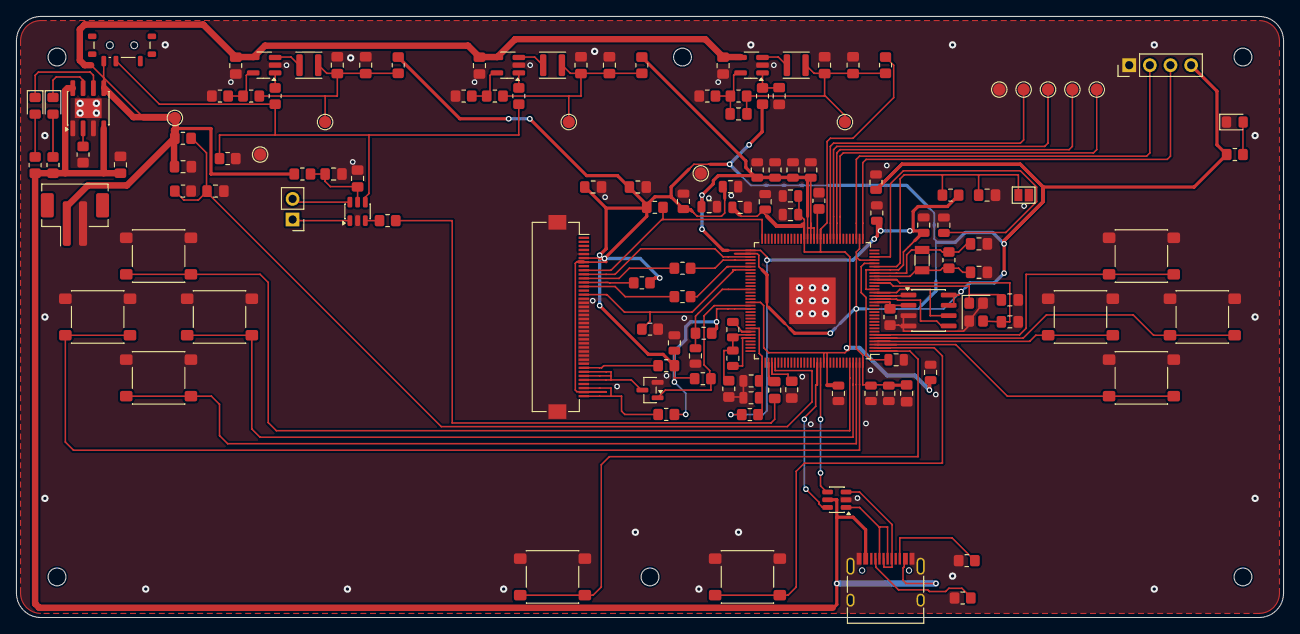
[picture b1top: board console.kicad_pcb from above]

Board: 2 copper layers, 156.0 x 74.0 mm, 141 parts (0 on the bottom side), 84 nets.

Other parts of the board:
H1, H2, H3, H4, H5, H6: MountingHole_2.2mm_M2

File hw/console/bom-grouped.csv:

Кол,Номинал,Корпус,Позиции
18,0.1u,Capacitor_SMD:C_0805_2012Metric,C802 C803 C804 C805 C807 C808 C809 C810 C811 C812 C814 C815 C816 C817 C818 C820 C824 C825
14,10k,Resistor_SMD:R_0805_2012Metric_Pad1.20x1.40mm_HandSolder,R19 R401 R402 R403 R406 R407 R408 R410 R504 R602 R606 R607 R608 R609
9,0.1u,Capacitor_SMD:C_0805_2012Metric_Pad1.18x1.45mm_HandSolder,C7 C8 C9 C14 C19 C401 C402 C503 C601
8,0,Resistor_SMD:R_0805_2012Metric_Pad1.20x1.40mm_HandSolder,R16 R17 R18 R503 R601 R801 R803 R804
7,10u,Capacitor_SMD:C_0805_2012Metric_Pad1.18x1.45mm_HandSolder,C12 C13 C403 C501 C502 C505 C602
6,22u,Capacitor_SMD:C_0805_2012Metric_Pad1.18x1.45mm_HandSolder,C1 C2 C3 C4 C5 C6
5,22p,Capacitor_SMD:C_0805_2012Metric_Pad1.18x1.45mm_HandSolder,C10 C15 C16 C17 C18
5,1k,Resistor_SMD:R_0805_2012Metric_Pad1.20x1.40mm_HandSolder,R7 R8 R12 R13 R901
5,33,Resistor_SMD:R_0805_2012Metric_Pad1.20x1.40mm_HandSolder,R404 R405 R603 R604 R605
4,2.2u,Capacitor_SMD:C_0805_2012Metric,C819 C821 C822 C823
3,10u,Capacitor_SMD:C_0805_2012Metric,C801 C806 C813
3,2.2u,Inductor_SMD:L_Sunlord_SWPA3015S,L1 L2 L3
3,150k,Resistor_SMD:R_0805_2012Metric_Pad1.20x1.40mm_HandSolder,R2 R4 R6
3,47k,Resistor_SMD:R_0805_2012Metric_Pad1.20x1.40mm_HandSolder,R10 R501 R502
3,GND,TestPoint:TestPoint_Pad_D1.5mm,TP5 TP802 TP905
3,SY8089AAAC,Package_TO_SOT_SMD:SOT-23-5_HandSoldering,U2 U3 U4
2,0.47u,Capacitor_SMD:C_0805_2012Metric,C826 C827
2,680k,Resistor_SMD:R_0805_2012Metric_Pad1.20x1.40mm_HandSolder,R1 R20
2,5.1k,Resistor_SMD:R_0805_2012Metric_Pad1.20x1.40mm_HandSolder,R301 R302
2,2.2k,Resistor_SMD:R_0805_2012Metric_Pad1.20x1.40mm_HandSolder,R409 R411
1,0.47u,Capacitor_SMD:C_0805_2012Metric_Pad1.18x1.45mm_HandSolder,C11
1,1u,Capacitor_SMD:C_0805_2012Metric_Pad1.18x1.45mm_HandSolder,C504
1,красный,LED_SMD:LED_0805_2012Metric_Pad1.15x1.40mm_HandSolder,D1
1,зелёный,LED_SMD:LED_0805_2012Metric_Pad1.15x1.40mm_HandSolder,D2
1,USBLC6-2SC6,Package_TO_SOT_SMD:SOT-23-6,D301
1,жёлтый,LED_SMD:LED_0805_2012Metric_Pad1.15x1.40mm_HandSolder,D901
1,Batt,Connector_PinHeader_2.54mm:PinHeader_1x02_P2.54mm_Vertical,J1
1,USB-C 16P,Connector_USB:USB_C_Receptacle_HRO_TYPE-C-31-M-12,J301
1,DM3AT-SF-PEJM5,Connector_Card:microSD_HC_Hirose_DM3AT-SF-PEJM5,J401
1,SPK 8R,Connector_PinHeader_2.54mm:PinHeader_1x02_P2.54mm_Vertical,J501
1,FFC-40 0.5mm,console:FH12-40S-0.5SH_ContactsReversed,J601
1,UART,Connector_PinHeader_2.54mm:PinHeader_1x04_P2.54mm_Vertical,J901
1,RESET,Jumper:SolderJumper-2_P1.3mm_Open_Pad1.0x1.5mm,JP1
1,FEL,Jumper:SolderJumper-2_P1.3mm_Open_Pad1.0x1.5mm,JP301
1,AO3400A,Package_TO_SOT_SMD:SOT-23,Q601
1,300k,Resistor_SMD:R_0805_2012Metric_Pad1.20x1.40mm_HandSolder,R3
1,75k,Resistor_SMD:R_0805_2012Metric_Pad1.20x1.40mm_HandSolder,R5
1,1M,Resistor_SMD:R_0805_2012Metric_Pad1.20x1.40mm_HandSolder,R9
1,1.1k,Resistor_SMD:R_0805_2012Metric_Pad1.20x1.40mm_HandSolder,R11
1,100k,Resistor_SMD:R_0805_2012Metric_Pad1.20x1.40mm_HandSolder,R14
1,68k,Resistor_SMD:R_0805_2012Metric_Pad1.20x1.40mm_HandSolder,R15
1,240,Resistor_SMD:R_0805_2012Metric_Pad1.20x1.40mm_HandSolder,R802
1,Движок,Button_Switch_SMD:SW_SPDT_Shouhan_MSK12C02,SW1
1,UP,Button_Switch_SMD:SW_SPST_PTS645Sx43SMTR92,SW101
1,DOWN,Button_Switch_SMD:SW_SPST_PTS645Sx43SMTR92,SW102
1,LEFT,Button_Switch_SMD:SW_SPST_PTS645Sx43SMTR92,SW103
1,RIGHT,Button_Switch_SMD:SW_SPST_PTS645Sx43SMTR92,SW104
1,SELECT,Button_Switch_SMD:SW_SPST_PTS645Sx43SMTR92,SW105
1,START,Button_Switch_SMD:SW_SPST_PTS645Sx43SMTR92,SW106
1,A,Button_Switch_SMD:SW_SPST_PTS645Sx43SMTR92,SW107
1,B,Button_Switch_SMD:SW_SPST_PTS645Sx43SMTR92,SW108
1,C,Button_Switch_SMD:SW_SPST_PTS645Sx43SMTR92,SW109
1,D,Button_Switch_SMD:SW_SPST_PTS645Sx43SMTR92,SW110
1,+3V3,TestPoint:TestPoint_Pad_D1.5mm,TP1
1,+1V8,TestPoint:TestPoint_Pad_D1.5mm,TP2
1,+0V9,TestPoint:TestPoint_Pad_D1.5mm,TP3
1,VSYS,TestPoint:TestPoint_Pad_D1.5mm,TP4
1,REFCLK,TestPoint:TestPoint_Pad_D1.5mm,TP801
1,TMS,TestPoint:TestPoint_Pad_D1.5mm,TP901
1,TDI,TestPoint:TestPoint_Pad_D1.5mm,TP902
1,TDO,TestPoint:TestPoint_Pad_D1.5mm,TP903
1,TCK,TestPoint:TestPoint_Pad_D1.5mm,TP904
1,F133-A,console:eLQFP-128_14x14_Pitch0.4mm_EPAD_5.72mm,U1
1,TP4056,Package_SO:SOIC-8-1EP_3.9x4.9mm_P1.27mm_EP2.41x3.3mm,U5
1,W25Q32JVSSIQ,Package_SO:SOIC-8_5.3x5.3mm_P1.27mm,U401
1,PAM8301,Package_TO_SOT_SMD:SOT-23-6,U501
1,24 МГц,Crystal:Crystal_SMD_3225-4Pin_3.2x2.5mm_HandSoldering,Y1
1,32.768 кГц,Crystal:Crystal_SMD_3215-2Pin_3.2x1.5mm,Y2

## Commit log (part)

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2026-01-29 docs
2026-01-31 UART
